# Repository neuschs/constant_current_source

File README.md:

# Constant Current Source
"Precise" Constant Current Source based on TI XTR110AG

# Main Components 

## Revision 0.1
### Arduino Nano
Simple Arduino for processing of the SCPI commands and coordinating the range switching.
### MCP3202
Two channel SPI 12 Bit ADC with external reference voltage.
### REF02
Reference voltage source used for internal "calibration" and as reference for arduino ADC and MCP3202

# Measurments
## Revision 0.1
### Stability over 2 Hours
Measured against reference voltage source REF02

#### Parameters:
- Duration: 2 Hours
- Frequency: 1s (approx.)
- Attentuatuation before LM324N: 8 (rough setting)
- LSB at ADC: approx 9,765mV (with Attentuation of 8)
- Internal Averaging Samples: 50

### Voltage A (Sense A):
| Value | Measurment |
| ------------------| ---------- |
|Standard Deviation| 1,456 mV    |
|Maximum Value|      5.216500 V  |
|Minimum Value|      5.207500 V  |
|Mean Value|         5.213059 V  |
|25% of Counts|      5.212000 V  |
|50% of Coutns|      5.213200 V  |
|75% of Counts|      5.214200 V  |

### Boxplot and Histogram

### Voltage B (Sense B):
| Value | Measurment |
| ------------------| ----------  |
|Standard Deviation| 411 uV       |
|Maximum Value:    |  5.150300 V  |
|Minimum Value:    |  5.146000 V  |
|Mean Value:       |  5.147937 V  |
|25% of Counts:    |  5.147700 V  |
|50% of Coutns:    |  5.147900 V  |
|75% of Counts:    |  5.148100 V  |

### Boxplot and Histogram

### Overview over 2 Hours

### Result
> In some mysterious way, Sense A voltage measrument is way more bad than Sense B. Next measurment will be done over 24h with better shielding against the USB connection which is directly over the input attentuation voltage divider.

# Credits
Used Librarys:

[vrekrer/Vrekrer SCPI parser@0.4.1](https://github.com/Vrekrer/Vrekrer_scpi_parser)

[robtillaart/PCF8574@0.3.2](https://github.com/RobTillaart/PCF8574)

[mokolea/InputDebounce@1.6.0](https://github.com/Mokolea/InputDebounce)

[ouviksaha97/MCP3202@1.0.2](https://github.com/souviksaha97/MCP3202)

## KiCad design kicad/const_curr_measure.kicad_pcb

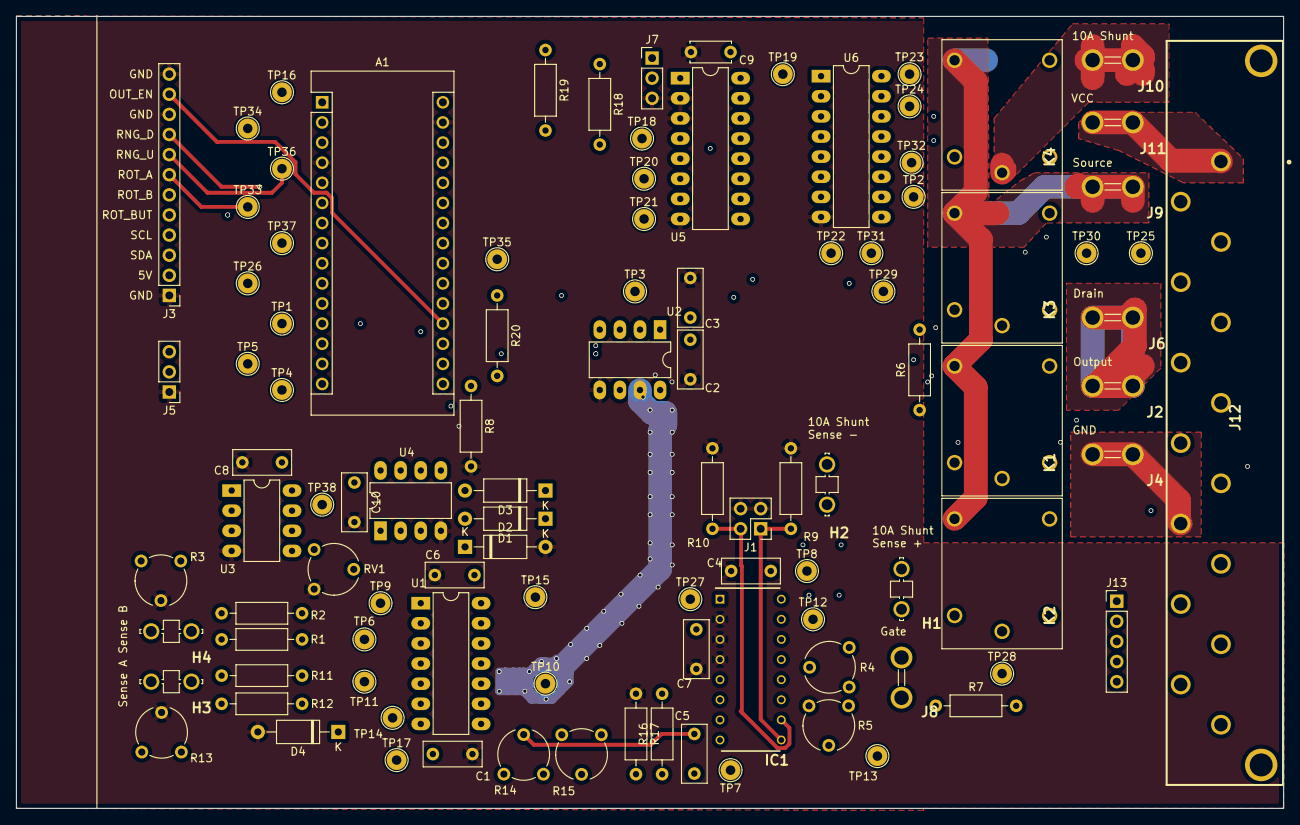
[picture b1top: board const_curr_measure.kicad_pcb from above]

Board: 4 copper layers, 160.0 x 100.0 mm, 102 parts (0 on the bottom side), 70 nets.

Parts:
A1: Arduino_Nano_v3.x; Arduino_Nano
C1, C2, C5, C6, C7, C8, C10: 100nF; C_Rect_L7.2mm_W3.0mm_P5.00mm_FKS2_FKP2_MKS2_MKP2
C3: 10uF Tantal; C_Rect_L7.2mm_W3.0mm_P5.00mm_FKS2_FKP2_MKS2_MKP2
C4: 1uF Tantal; C_Rect_L7.2mm_W3.0mm_P5.00mm_FKS2_FKP2_MKS2_MKP2
C9: 100nF; C_Disc_D5.0mm_W2.5mm_P5.00mm
D1, D2, D3, D4: D_Schottky; D_A-405_P10.16mm_Horizontal
H1, H2, H3, H4: 63823-1; 638231
IC1: XTR110AG; CDIP774W53P254L2057H445Q16
J1: Conn_02x02_Counter_Clockwise; PinHeader_2x02_P2.54mm_Vertical
J2, J4, J6, J8, J9, J10, J11: 1-726386-2; 17263862
J3: Conn_01x12; PinHeader_1x12_P2.54mm_Vertical
J5, J7: Conn_01x03; PinHeader_1x03_P2.54mm_Vertical
J12: 09061152911; 09061152911_2
J13: Conn_01x05; PinHeader_1x05_P2.54mm_Vertical
K1, K2, K3, K4: 36.11.9.005.4011; 36SERIES-MINIATURE-PCB-RELAYS-10A
R1, R11, R17: 100k; R_Axial_DIN0207_L6.3mm_D2.5mm_P10.16mm_Horizontal
R2, R8, R12: 10k; R_Axial_DIN0207_L6.3mm_D2.5mm_P10.16mm_Horizontal
R3, R4, R13: 10k; Potentiometer_Piher_PT-6-V_Vertical
R5, R15: 1k; Potentiometer_Piher_PT-6-V_Vertical
R6: 1; R_Axial_DIN0207_L6.3mm_D2.5mm_P10.16mm_Horizontal
R7: 10; R_Axial_DIN0207_L6.3mm_D2.5mm_P10.16mm_Horizontal
R9, R10, R18, R19: R; R_Axial_DIN0207_L6.3mm_D2.5mm_P10.16mm_Horizontal
R14: 47k; Potentiometer_Piher_PT-6-V_Vertical
R16: 82k; R_Axial_DIN0207_L6.3mm_D2.5mm_P10.16mm_Horizontal
R20: 4k7; R_Axial_DIN0207_L6.3mm_D2.5mm_P10.16mm_Horizontal
RV1: 10k; Potentiometer_Piher_PT-6-V_Vertical
TP1, TP2, TP3, TP4, TP5, TP6, TP7, TP8, TP9, TP10, TP11, TP12, TP13, TP14, TP15, TP16, TP17, TP18, TP19, TP20, TP21, TP22, TP23, TP24, TP25, TP26, TP27, TP28, TP29, TP30, TP31, TP32, TP33, TP34, TP35, TP36, TP37, TP38: 1018.68; TestPoint_THTPad_D2.5mm_Drill1.2mm
U1: LM324; DIP-14_W7.62mm_LongPads
U2: MCP4821; DIP-8_W7.62mm_LongPads
U3: REF02CP; DIP-8_W7.62mm_LongPads
U4: MCP3202; DIP-8_W7.62mm_LongPads
U5: PCF8574; DIP-16_W7.62mm_LongPads
U6: ULN2003; DIP-16_W7.62mm_LongPads

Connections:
4mA_Span: IC1.10, J1.2, R10.2
16m_Span: IC1.9, J1.1, R9.1
20mA_Shunt: IC1.1, K1.5, TP8.1, TP27.1
100mA_Shunt: K2.5, R7.2, TP28.1
1000ma_Shunt: K3.5, R6.2, TP29.1
10000mA_Shunt_+: C4.1, C7.1, H1.1, H1.2, IC1.16, J11.1, J11.2, J12.1, R6.1, R7.1
10000mA_Shunt_-: J10.1, J10.2, K4.5, TP30.1
10000mA_Shunt_Sense_-: H2.1, H2.2, IC1.13, J9.1, J9.2, K1.3, K2.3, K3.3, K4.3
+5F: C10.1, RV1.3, TP38.1, U3.6, U4.8
+5V: C2.1, C3.1, C9.1, D1.1, D3.1, J3.2, J5.3, J7.1, J12.9, K1.4, K2.4, K3.4, K4.4, R18.1, R19.1, R20.2, TP16.1, U2.1, U5.16, U6.9
+12V: A1.30, C1.1, C8.1, J12.8, U1.4, U3.2
-12V: C6.2, J12.7, U1.11
ADC0: D3.2, D4.1, TP14.1, U1.6, U1.7, U4.2
ADC1: D1.2, D2.1, TP9.1, U1.1, U1.2, U4.3
ADC_CS: A1.11, U4.1
DAC_CS: A1.13, TP3.1, U2.2
DAC_OUT: TP10.1, U1.10, U2.8
DAC_OUT_FULL_SWING: C5.1, IC1.5, R14.2, TP17.1, U1.8
DAC_SHDN: A1.12, R8.1, TP1.1, U2.6
FET_DRAIN: J2.1, J2.2, J6.1, J6.2
FET_GATE: IC1.14, J8.1, J8.2
GND: A1.4, A1.29, C1.2, C2.2, C3.2, C4.2, C6.1, C7.2, C8.2, C9.2, C10.2, D2.2, D4.2, IC1.2, IC1.3, IC1.4, J1.3, J1.4, J3.1, J3.10, J3.12, J4.1, J4.2, J5.1, J7.3, J12.10, R3.2, R8.2, R9.2, R10.1, R13.2, R17.1, RV1.1, TP15.1, U2.5, U2.7, U3.4, U4.4, U5.2, U5.3, U5.8, U6.8
I2C_A0: J7.2, U5.1
unnamed: C5.2, R16.1, R17.2, U1.9
unnamed: IC1.8, TP7.1
unnamed: IC1.11, TP13.1
unnamed: IC1.12, IC1.15, TP12.1
unnamed: J12.11, J13.1
unnamed: J12.12, J13.2
unnamed: J12.13, J13.3
unnamed: J12.14, J13.4
unnamed: J12.15, J13.5
unnamed: K1.1, TP22.1, U6.16
unnamed: K2.1, TP23.1, U6.15
unnamed: K3.1, TP24.1, U6.14
unnamed: K4.1, TP25.1, U6.13
unnamed: R1.2, R2.1, TP6.1, U1.3
unnamed: R2.2, R3.1
unnamed: R4.2, R5.1
unnamed: R11.2, R12.1, TP11.1, U1.5
unnamed: R12.2, R13.1
unnamed: R14.1, R15.2
unnamed: R15.1, R16.2
unnamed: RV1.2, U3.5
unnamed: TP2.1, U6.10
unnamed: TP18.1, U5.4, U6.1
unnamed: TP19.1, U5.5, U6.2
unnamed: TP20.1, U5.6, U6.3
unnamed: TP21.1, U5.7, U6.4
unnamed: TP31.1, U6.12
unnamed: TP32.1, U6.11
unnamed: U5.9, U6.7
unnamed: U5.10, U6.6
unnamed: U5.11, U6.5
OUTPUT_ENABLE: A1.19, J3.11
OUT_SENSE_A: H3.1, H3.2, R11.1
OUT_SENSE_B: H4.1, H4.2, R1.1
RANGE_DOWN: A1.8, J3.9, TP35.1
RANGE_UP: A1.7, J3.8, TP36.1
ROT_POT_A: A1.6, J3.7, TP33.1
ROT_POT_B: A1.5, J3.6, TP34.1
Rot_Enc_But: A1.9, J3.5, TP37.1
SCL: A1.24, J3.4, R19.2, U5.14
SDA: A1.23, J3.3, R18.2, U5.15
SPI_MISO: A1.15, U4.6
SPI_MOSI: A1.14, TP5.1, U2.4, U4.5
SPI_SCK: A1.16, TP4.1, U2.3, U4.7
TEMP_SENS_OW: A1.10, J5.2, R20.1, TP26.1
ZERO_ADJUST_A: IC1.6, R4.1
ZERO_ADJUST_B: IC1.7, R5.2

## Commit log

2021-07-05 * initial commit
2021-07-05 * most pcb routing
2021-07-06 * nearly finished pcb, changed front pcb connector to one big * added output enable switch net
2021-07-06 * first revision will order this version
2021-07-28 * addded Ibom * added normal bom
2021-08-03 * initial commit of "firmware"
2021-08-03 * changed some stuff
2021-08-10 Set theme jekyll-theme-cayman
2021-09-24 current working changes for revision 0.2
